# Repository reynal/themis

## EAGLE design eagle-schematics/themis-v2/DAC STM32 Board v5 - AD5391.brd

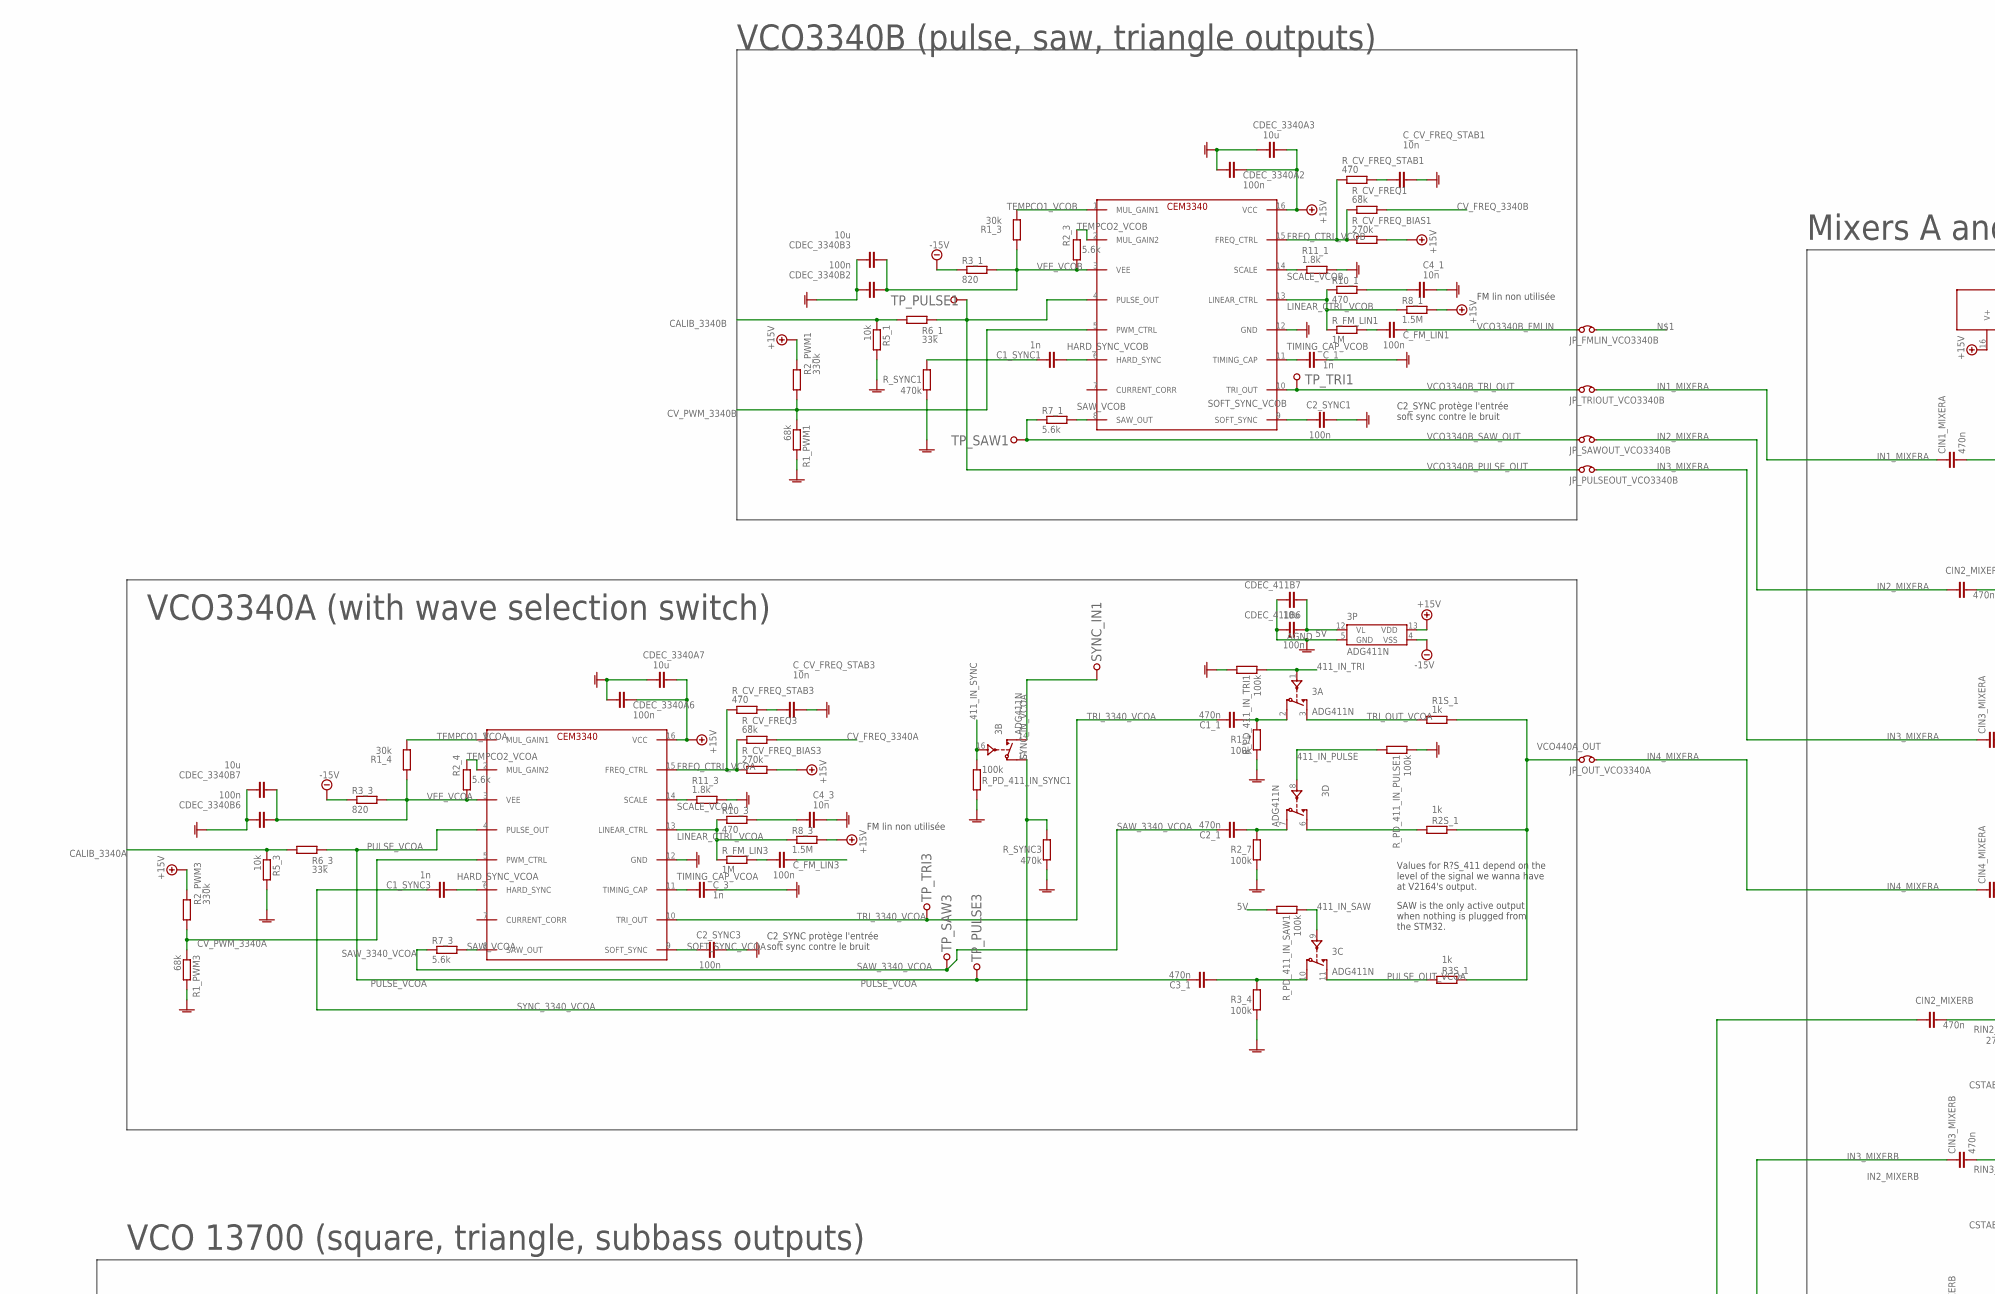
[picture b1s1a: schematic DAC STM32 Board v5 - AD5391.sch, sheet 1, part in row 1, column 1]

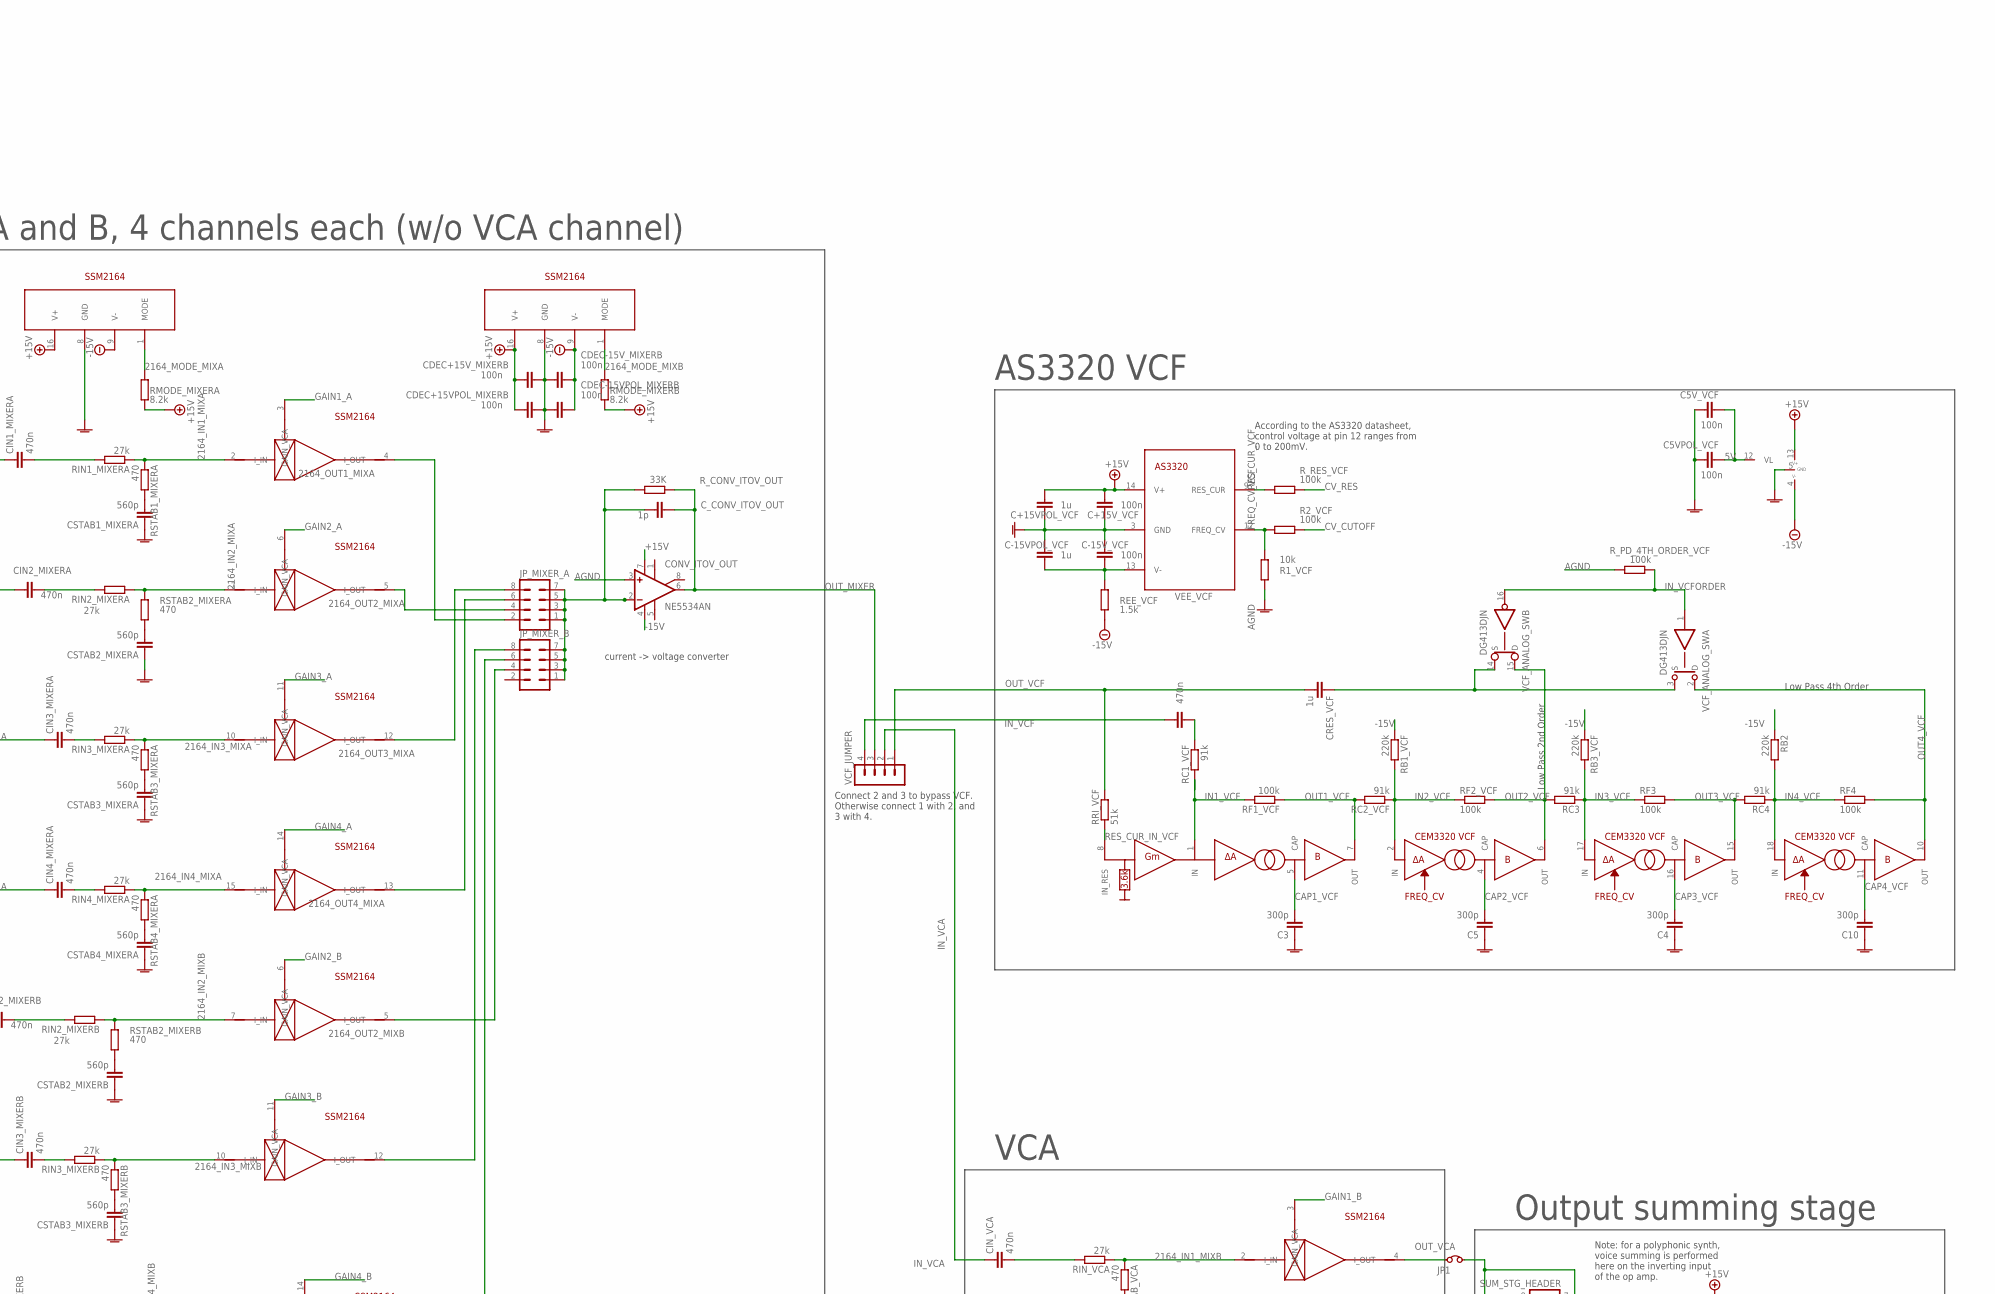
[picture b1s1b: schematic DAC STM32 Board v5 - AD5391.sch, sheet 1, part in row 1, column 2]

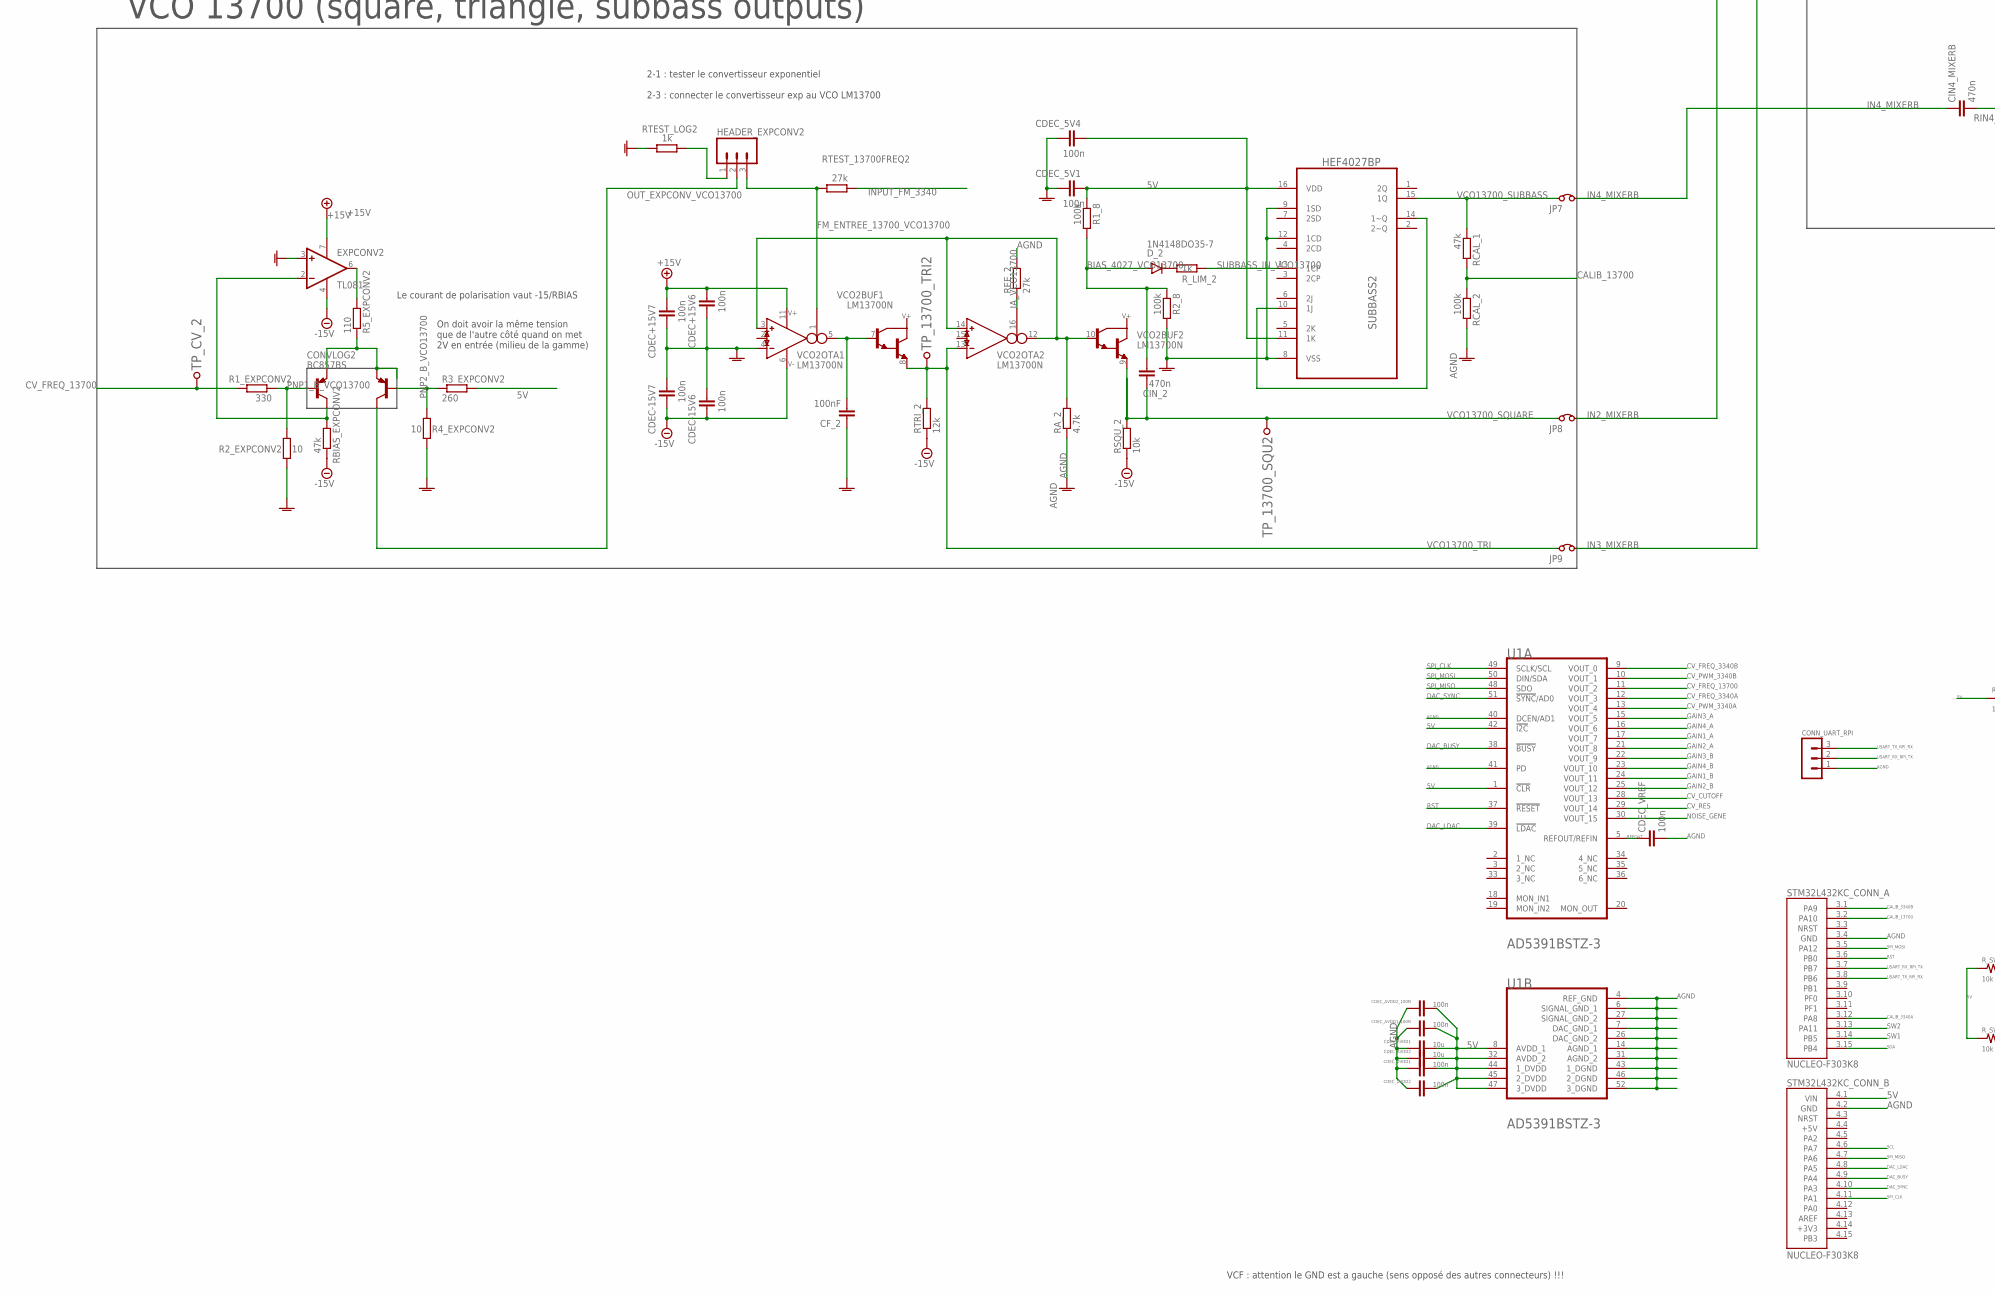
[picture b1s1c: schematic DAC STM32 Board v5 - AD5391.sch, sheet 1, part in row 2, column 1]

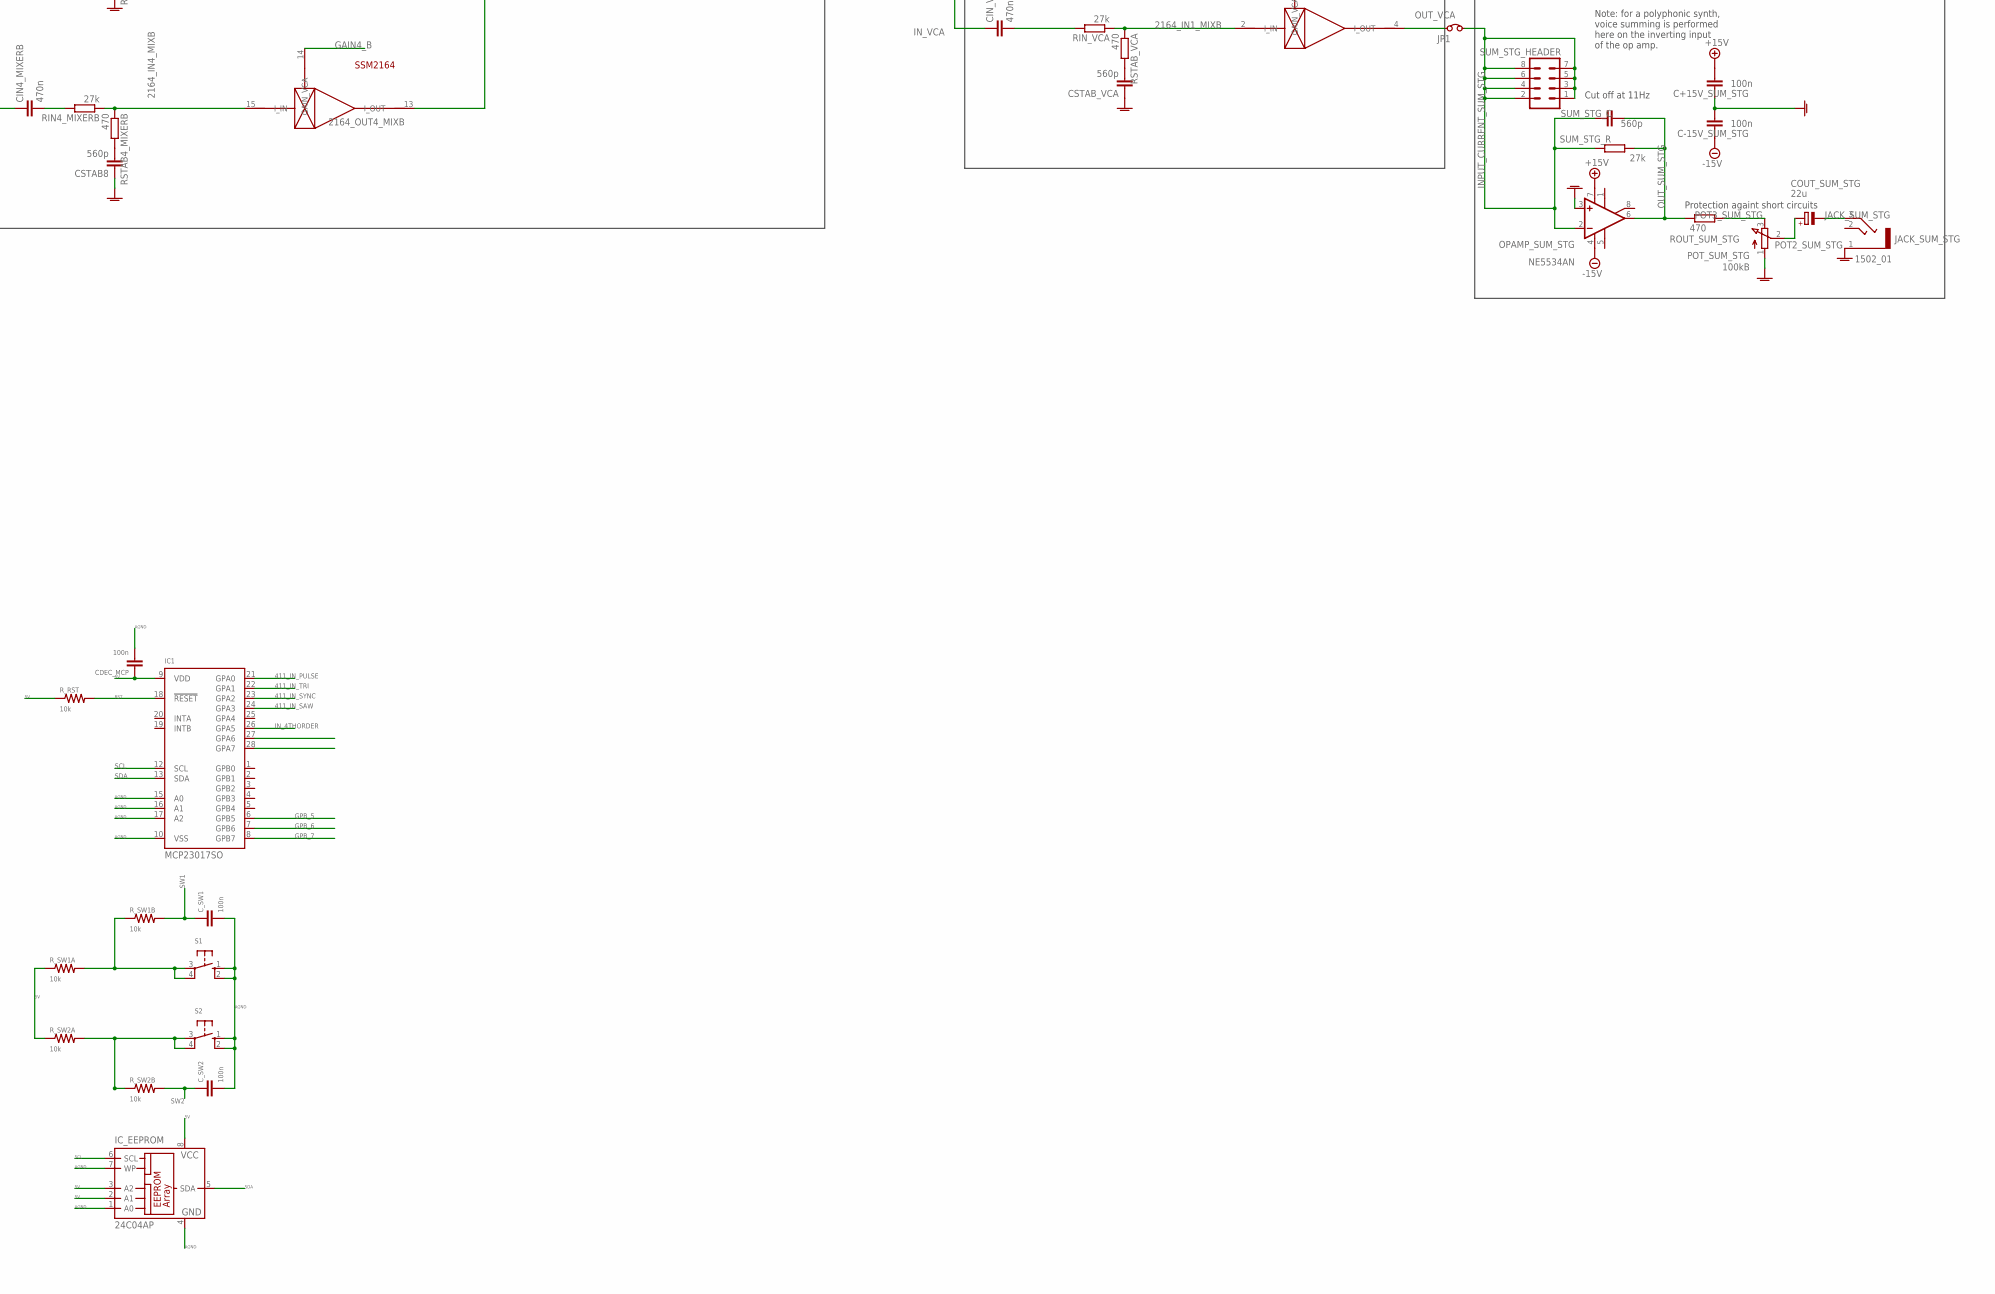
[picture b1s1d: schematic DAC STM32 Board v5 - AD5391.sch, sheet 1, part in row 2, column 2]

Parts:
3: ADG411N; DIL16
C1_1, C2_1: 470n; C075-032X103
C1_SYNC1, C1_SYNC3: 1n; C075-032X103
C2_SYNC1, C5VPOL_VCF, C5V_VCF: 100n; C075-032X103
C2_SYNC3: 100n; C050-025X075
C3, C4, C5, C10: 300p; C075-032X103
C3_1: 470n; C102-043X133
C4_1, C4_3: 10n; C050-025X075
C+15VPOL_VCF: 1u; C075-032X103
C+15V_SUM_STG, C+15V_VCF: 100n; C075-032X103
C-15VPOL_VCF: 1u; C075-032X103
C-15V_SUM_STG, C-15V_VCF: 100n; C075-032X103
CDEC+15V6, CDEC+15VPOL_MIXERB: 100n; C075-032X103
CDEC+15V7: 100n; C050-025X075
CDEC+15V_MIXERB: 100n; C050-030X075
CDEC-15V6: 100n; C050-025X075
CDEC-15V7: 100n; C075-032X103
CDEC-15VPOL_MIXERB, CDEC-15V_MIXERB: 100n; C050-030X075
CDEC_5V1, CDEC_5V4, CDEC_411B6, CDEC_3340A2, CDEC_3340A6, CDEC_3340B2, CDEC_3340B6: 100n; C050-025X075
CDEC_411B7, CDEC_3340A7, CDEC_3340B3, CDEC_3340B7: 10u; C050-025X075
CDEC_3340A3: 10u; C075-032X103
CDEC_AVDD1, CDEC_AVDD2: 10u; C050-030X075
CDEC_AVDD1_100N, CDEC_AVDD2_100N: 100n; C050-030X075
CDEC_DVDD1: 100n; C075-032X103
CDEC_DVDD2: 100n; C050-030X075
CDEC_MCP: 100n; C075-032X103
CDEC_VREF: 100n; C050-030X075
CEM1, CEM3: CEM3340; DIL16
CF_2: 100nF; C050-025X075
CIN1_MIXERA, CIN2_MIXERA, CIN2_MIXERB, CIN3_MIXERA, CIN3_MIXERB, CIN4_MIXERA, CIN4_MIXERB: 470n; C050-030X075
CIN_2: 470n; C050-025X075
CIN_VCA: 470n; C050-030X075
CONN_UART_RPI: MA03-1
CONVLOG2: BC857BS; DIL06
CONV_ITOV_OUT: NE5534AN; DIL08
COUT_SUM_STG: 22u; B45181A
CRES_VCF: 1u; C075-032X103
CSTAB1_MIXERA, CSTAB2_MIXERA, CSTAB2_MIXERB, CSTAB3_MIXERA, CSTAB3_MIXERB, CSTAB4_MIXERA, CSTAB8: 560p; C050-030X075
CSTAB_VCA: 560p; C050-030X075
C_1, C_3: 1n; C050-025X075
C_CONV_ITOV_OUT: 1p; C050-030X075
C_CV_FREQ_STAB1, C_CV_FREQ_STAB3: 10n; C075-032X103
C_FM_LIN1, C_FM_LIN3: 100n; C050-025X075
C_IN2: 470n; C050-025X075
C_SW1, C_SW2: 100n; C050-030X075
D_2: 1N4148DO35-7; DO35-7
EXPCONV2: TL081; DIL08
HEADER_EXPCONV2: M03; 03P
IC1: MCP23017SO; SO28W
IC_EEPROM: 24C04AP; DIL8
JACK_SUM_STG: 1502_01
JP1, JP7, JP8, JP9: JUMPER; HDR2X1
JP_FMLIN_VCO3340B: JUMPER; HDR2X1
JP_MIXER_A: MA04-2
JP_MIXER_B: MA04-2
JP_OUT_VCO3340A: JUMPER; HDR2X1
JP_PULSEOUT_VCO3340B: JUMPER; HDR2X1
JP_SAWOUT_VCO3340B: JUMPER; HDR2X1
JP_TRIOUT_VCO3340B: JUMPER; HDR2X1
MIXER_A: SSM2164_MULTI; DIL16
MIXER_B: SSM2164_MULTI; DIL16
OPAMP_SUM_STG: NE5534AN; DIL08
POT_SUM_STG: 100kB; 3RP/1610N
R1S_1, R2S_1: 1k; 0204/7
R1_3, R1_4: 30k; 0204/7
R1_7, R1_8, R2_8, R2_VCF: 100k; 0204/7
R1_EXPCONV2: 330; 0204/7
R1_PWM1: 68k; 0204/7
R1_PWM3: 68k; 0207/10
R1_VCF, R5_1, R5_3: 10k; 0204/7
R2_3, R2_4: 5.6k; 0204/7
R2_7, R3_4: 100k; 0207/10
R2_EXPCONV2, R4_EXPCONV2: 10; 0204/7
R2_PWM1, R2_PWM3: 330k; 0204/7
R3S_1: 1k; 0207/10
R3_1, R3_3: 820; 0204/7
R3_EXPCONV2: 260; 0204/7
R5_EXPCONV2: 110; 0204/7
R6_1, R6_3: 33k; 0204/7
R7_1, R7_3: 5.6k; 0207/10
R8_1, R8_3: 1.5M; 0204/7
R10_1, R10_3: 470; 0204/7
R11_1, R11_3: 1.8k; 0204/7
RA_2: 4.7k; 0204/7
RB1_VCF, RB2, RB3_VCF: 220k; 0204/7
RBIAS_EXPCONV2: 47k; 0204/7
RC1_VCF, RC2_VCF, RC3, RC4: 91k; 0204/7
RCAL_1: 47k; 0204/7
RCAL_2: 100k; 0204/7
REE_2: 27k; 0204/7
REE_VCF: 1.5k; 0207/10
RF1_VCF: 100k; 0207/10
RF2_VCF, RF3, RF4: 100k; 0204/7
RIN1_MIXERA, RIN2_MIXERB, RIN3_MIXERA, RIN3_MIXERB, RIN4_MIXERA, RIN4_MIXERB: 27k; 0204/7
RIN2_MIXERA: 27k; 0207/10
RIN_VCA: 27k; 0204/7
RMODE_MIXERA: 8.2k; 0204/7
RMODE_MIXERB: 8.2k; 0204/7
ROUT_SUM_STG: 470; 0207/12
RRI_VCF: 51k; 0207/10
RSQU_2: 10k; 0204/7
RSTAB1_MIXERA, RSTAB3_MIXERA, RSTAB3_MIXERB, RSTAB4_MIXERA, RSTAB4_MIXERB: 470; 0204/7
RSTAB2_MIXERA, RSTAB2_MIXERB: 470; 0207/10
RSTAB_VCA: 470; 0204/7
RTEST_13700FREQ2: 27k; 0204/7
RTEST_LOG2: 1k; 0204/7
RTRI_2: 12k; 0204/7
R_CONV_ITOV_OUT: 33K; 0204/7
R_CV_FREQ1, R_CV_FREQ3: 68k; 0204/7
R_CV_FREQ_BIAS1, R_CV_FREQ_BIAS3: 270k; 0204/7
R_CV_FREQ_STAB1, R_CV_FREQ_STAB3: 470; 0204/7
R_FM_LIN1, R_FM_LIN3: 1M; 0204/7
R_LIM_2: 1k; 0204/7
R_PD_4TH_ORDER_VCF, R_PD_411_IN_SAW1, R_PD_411_IN_SYNC1, R_PD_411_IN_TRI1: 100k; 0204/7
R_PD_411_IN_PULSE1: 100k; 0207/10
R_RES_VCF: 100k; 0204/7
R_RST: 10k; 0207/10
R_SW1A, R_SW1B, R_SW2A, R_SW2B: 10k; 0207/10
R_SYNC1, R_SYNC3: 470k; 0204/7
S1, S2: 10-XX; B3F-10XX
STM32L432KC_CONN_: NUCLEO-F303K8; MODULE_NUCLEO-F303K8
SUBBASS2: HEF4027BP; DIP254P762X420-16
SUM_STG_C: 560p; C075-032X103
SUM_STG_HEADER: MA04-2
SUM_STG_R: 27k; 0207/10
SYNC_IN1: TESTPOINT; TESTPOINT_63
TP_13700_SQU2, TP_13700_TRI2: TESTPOINT; TESTPOINT_63
TP_CV_2: TESTPOINT; TESTPOINT_63
TP_PULSE1, TP_PULSE3: TESTPOINT; TESTPOINT_63
TP_SAW1, TP_SAW3: TESTPOINT; TESTPOINT_63
TP_TRI1, TP_TRI3: TESTPOINT; TESTPOINT_63
U1: ANALOG_DEVICES_AD5391BSTZ-3ANALOG_DEVICES_AD5391B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; ANALOG_DEVICES_AD5391BSTZ-3_0
VCF: AS3320; DIL18
VCF_ANALOG_SW: DG413DJN; DIL16
VCF_JUMPER: MA04-1
VCO2: LM13700N; DIL16

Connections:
5V: 3.12 (VL), C5VPOL_VCF.1, C5V_VCF.1, CDEC_5V1.1, CDEC_5V4.1, CDEC_411B6.1, CDEC_411B7.1, CDEC_AVDD1.2, CDEC_AVDD1_100N.2, CDEC_AVDD2.2, CDEC_AVDD2_100N.2, CDEC_DVDD1.2, CDEC_DVDD2.2, CDEC_MCP.1, IC1.9 (VDD), IC_EEPROM.2 (A1), IC_EEPROM.3 (A2), IC_EEPROM.8 (VCC), R1_8.1, R3_EXPCONV2.2, R_PD_411_IN_SAW1.2, R_RST.1, R_SW1A.1, R_SW2A.1, STM32L432KC_CONN_.4.1 (VIN), SUBBASS2.11 (1K), SUBBASS2.16 (VDD), U1.1 (!CLR!), U1.8 (AVDD_1), U1.32 (AVDD_2), U1.42 (!I2C!), U1.44 (1_DVDD), U1.45 (2_DVDD), U1.47 (3_DVDD), VCF_ANALOG_SW.12 (VL)
411_IN_PULSE: 3.8 (IN), IC1.21 (GPA0), R_PD_411_IN_PULSE1.2
411_IN_SAW: 3.9 (IN), IC1.24 (GPA3), R_PD_411_IN_SAW1.1
411_IN_SYNC: 3.16 (IN), IC1.23 (GPA2), R_PD_411_IN_SYNC1.1
411_IN_TRI: 3.1 (IN), IC1.22 (GPA1), R_PD_411_IN_TRI1.1
2164_IN1_MIXA: MIXER_A.2 (I_IN), RIN1_MIXERA.1, RSTAB1_MIXERA.1
2164_IN1_MIXB: MIXER_B.2 (I_IN), RIN_VCA.1, RSTAB_VCA.1
2164_IN2_MIXA: MIXER_A.7 (I_IN), RIN2_MIXERA.1, RSTAB2_MIXERA.1
2164_IN2_MIXB: MIXER_B.7 (I_IN), RIN2_MIXERB.1, RSTAB2_MIXERB.1
2164_IN3_MIXA: MIXER_A.10 (I_IN), RIN3_MIXERA.1, RSTAB3_MIXERA.1
2164_IN3_MIXB: MIXER_B.10 (I_IN), RIN3_MIXERB.1, RSTAB3_MIXERB.1
2164_IN4_MIXA: MIXER_A.15 (I_IN), RIN4_MIXERA.1, RSTAB4_MIXERA.1
2164_IN4_MIXB: MIXER_B.15 (I_IN), RIN4_MIXERB.1, RSTAB4_MIXERB.1
2164_MODE_MIXA: MIXER_A.1 (MODE), RMODE_MIXERA.2
2164_MODE_MIXB: MIXER_B.1 (MODE), RMODE_MIXERB.2
2164_OUT1_MIXA: JP_MIXER_A.2, MIXER_A.4 (I_OUT)
2164_OUT2_MIXA: JP_MIXER_A.4, MIXER_A.5 (I_OUT)
2164_OUT2_MIXB: JP_MIXER_B.4, MIXER_B.5 (I_OUT)
2164_OUT3_MIXA: JP_MIXER_A.8, MIXER_A.12 (I_OUT)
2164_OUT3_MIXB: JP_MIXER_B.8, MIXER_B.12 (I_OUT)
2164_OUT4_MIXA: JP_MIXER_A.6, MIXER_A.13 (I_OUT)
2164_OUT4_MIXB: JP_MIXER_B.6, MIXER_B.13 (I_OUT)
+15V: 3.13 (VDD), C+15VPOL_VCF.2, C+15V_SUM_STG.2, C+15V_VCF.2, CDEC+15V6.1, CDEC+15V7.1, CDEC+15VPOL_MIXERB.2, CDEC+15V_MIXERB.2, CDEC_3340A2.2, CDEC_3340A3.2, CDEC_3340A6.2, CDEC_3340A7.2, CEM1.16 (VCC), CEM3.16 (VCC), CONV_ITOV_OUT.7 (V+), EXPCONV2.7 (V+), MIXER_A.16 (V+), MIXER_B.16 (V+), OPAMP_SUM_STG.7 (V+), R2_PWM1.2, R2_PWM3.2, R8_1.2, R8_3.2, RMODE_MIXERA.1, RMODE_MIXERB.1, R_CV_FREQ_BIAS1.2, R_CV_FREQ_BIAS3.2, VCF.14 (V+), VCF_ANALOG_SW.13 (V+), VCO2.11 (V+)
-15V: 3.4 (VSS), C-15V_SUM_STG.1, CDEC-15V6.2, CDEC-15V7.2, CDEC-15VPOL_MIXERB.1, CDEC-15V_MIXERB.1, CONV_ITOV_OUT.4 (V-), EXPCONV2.4 (V-), MIXER_A.9 (V-), MIXER_B.9 (V-), OPAMP_SUM_STG.4 (V-), R3_1.1, R3_3.1, RB1_VCF.1, RB2.1, RB3_VCF.1, RBIAS_EXPCONV2.1, REE_VCF.1, RSQU_2.1, RTRI_2.1, VCF_ANALOG_SW.4 (V-), VCO2.6 (V-)
AGND: 3.5 (GND), C2_SYNC1.1, C2_SYNC3.1, C3.1, C4.1, C4_1.2, C4_3.2, C5.1, C5VPOL_VCF.2, C5V_VCF.2, C10.1, C+15VPOL_VCF.1, C+15V_SUM_STG.1, C+15V_VCF.1, C-15VPOL_VCF.2, C-15V_SUM_STG.2, C-15V_VCF.2, CDEC+15V6.2, CDEC+15V7.2, CDEC+15VPOL_MIXERB.1, CDEC+15V_MIXERB.1, CDEC-15V6.1, CDEC-15V7.1, CDEC-15VPOL_MIXERB.2, CDEC-15V_MIXERB.2, CDEC_5V1.2, CDEC_5V4.2, CDEC_411B6.2, CDEC_411B7.2, CDEC_3340A2.1, CDEC_3340A3.1, CDEC_3340A6.1, CDEC_3340A7.1, CDEC_3340B2.1, CDEC_3340B3.1, CDEC_3340B6.1, CDEC_3340B7.1, CDEC_AVDD1.1, CDEC_AVDD1_100N.1, CDEC_AVDD2.1, CDEC_AVDD2_100N.1, CDEC_DVDD1.1, CDEC_DVDD2.1, CDEC_MCP.2, CDEC_VREF.2, CEM1.12 (GND), CEM3.12 (GND), CF_2.1, CONN_UART_RPI.1, CONV_ITOV_OUT.3 (+IN), CSTAB1_MIXERA.1, CSTAB2_MIXERA.1, CSTAB2_MIXERB.1, CSTAB3_MIXERA.1, CSTAB3_MIXERB.1, CSTAB4_MIXERA.1, CSTAB_VCA.1, C_1.1, C_3.1, C_CV_FREQ_STAB1.1, C_CV_FREQ_STAB3.1, C_SW1.2, C_SW2.2, EXPCONV2.3 (+IN), IC1.10 (VSS), IC1.15 (A0), IC1.16 (A1), IC1.17 (A2), IC_EEPROM.1 (A0), IC_EEPROM.4 (GND), IC_EEPROM.7 (WP), JACK_SUM_STG.1, MIXER_A.8 (GND), MIXER_B.8 (GND), OPAMP_SUM_STG.3 (+IN), POT_SUM_STG.1 (A), R1_7.1, R1_PWM1.2, R1_PWM3.2, R1_VCF.2, R2_7.1, R2_8.2, R2_EXPCONV2.2, R3_4.1, R4_EXPCONV2.2, R5_1.2, R5_3.2, R11_1.2, R11_3.2, RA_2.1, RCAL_2.2, REE_2.2, RTEST_LOG2.2, R_PD_4TH_ORDER_VCF.1, R_PD_411_IN_PULSE1.1, R_PD_411_IN_SYNC1.2, R_PD_411_IN_TRI1.2, R_SYNC1.1, R_SYNC3.1, S1.1 (S), S1.2 (S1), S2.1 (S), S2.2 (S1), STM32L432KC_CONN_.3.4 (GND), STM32L432KC_CONN_.4.2 (GND), SUBBASS2.8 (VSS), SUBBASS2.9 (1SD), SUBBASS2.12 (1CD), U1.4 (REF_GND), U1.6 (SIGNAL_GND_1), U1.7 (DAC_GND_1), U1.14 (AGND_1), U1.26 (DAC_GND_2), U1.27 (SIGNAL_GND_2), U1.31 (AGND_2), U1.40 (DCEN/AD1), U1.41 (PD), U1.43 (1_DGND), U1.46 (2_DGND), U1.52 (3_DGND), VCF.3 (GND), VCF_ANALOG_SW.5 (GND), VCO2.4 (IN_N)
BIAS_4027_VCO13700: CIN_2.1, D_2.A, R1_8.2, R2_8.1
CALIB_3340A: R5_3.1, R6_3.1, STM32L432KC_CONN_.3.12 (PA8)
CALIB_3340B: R5_1.1, R6_1.1, STM32L432KC_CONN_.3.1 (PA9)
CALIB_13700: RCAL_1.2, RCAL_2.1, STM32L432KC_CONN_.3.2 (PA10)
CAP1_VCF: C3.2, VCF.5 (CAP)
CAP2_VCF: C5.2, VCF.4 (CAP)
CAP3_VCF: C4.2, VCF.16 (CAP)
CAP4_VCF: C10.2, VCF.11 (CAP)
CSTAB3_MIXERB: CSTAB8.1
CV_CUTOFF: R2_VCF.2, U1.28 (VOUT_13)
CV_FREQ_3340A: R_CV_FREQ3.2, U1.12 (VOUT_3)
CV_FREQ_3340B: R_CV_FREQ1.2, U1.9 (VOUT_0)
CV_FREQ_13700: R1_EXPCONV2.2, TP_CV_2.P$1, U1.11 (VOUT_2)
CV_PWM_3340A: CEM3.5 (PWM_CTRL), R1_PWM3.1, R2_PWM3.1, U1.13 (VOUT_4)
CV_PWM_3340B: CEM1.5 (PWM_CTRL), R1_PWM1.1, R2_PWM1.1, U1.10 (VOUT_1)
CV_RES: R_RES_VCF.2, U1.29 (VOUT_14)
DAC_BUSY: STM32L432KC_CONN_.4.9 (PA4), U1.38 (!BUSY!)
DAC_LDAC: STM32L432KC_CONN_.4.8 (PA5), U1.39 (!LDAC!)
DAC_SYNC: STM32L432KC_CONN_.4.10 (PA3), U1.51 (!SYNC!/AD0)
FM_ENTREE_13700_VCO13700: HEADER_EXPCONV2.3, RTEST_13700FREQ2.2, VCO2.1 (I_BIAS)
FREQ_CTRL_VCOA: CEM3.15 (FREQ_CTRL), R_CV_FREQ3.1, R_CV_FREQ_BIAS3.1, R_CV_FREQ_STAB3.1
FREQ_CTRL_VCOB: CEM1.15 (FREQ_CTRL), R_CV_FREQ1.1, R_CV_FREQ_BIAS1.1, R_CV_FREQ_STAB1.1
FREQ_CV_VCF: R1_VCF.1, R2_VCF.1, VCF.12 (FREQ_CV)
GAIN1_A: MIXER_A.3 (GAIN_VCA), U1.17 (VOUT_7)
GAIN1_B: MIXER_B.3 (GAIN_VCA), U1.24 (VOUT_11)
GAIN2_A: MIXER_A.6 (GAIN_VCA), U1.21 (VOUT_8)
GAIN2_B: MIXER_B.6 (GAIN_VCA), U1.25 (VOUT_12)
GAIN3_A: MIXER_A.11 (GAIN_VCA), U1.15 (VOUT_5)
GAIN3_B: MIXER_B.11 (GAIN_VCA), U1.22 (VOUT_9)
GAIN4_A: MIXER_A.14 (GAIN_VCA), U1.16 (VOUT_6)
GAIN4_B: MIXER_B.14 (GAIN_VCA), U1.23 (VOUT_10)
GPB_5: IC1.6 (GPB5)
GPB_6: IC1.7 (GPB6)
GPB_7: IC1.8 (GPB7)
HARD_SYNC_VCOA: C1_SYNC3.2, CEM3.6 (HARD_SYNC)
HARD_SYNC_VCOB: C1_SYNC1.2, CEM1.6 (HARD_SYNC)
IA_VCO13700: REE_2.1, VCO2.16 (I_BIAS)
IN1_MIXERA: CIN1_MIXERA.1, JP_TRIOUT_VCO3340B.2
IN1_VCF: RC1_VCF.2, RF1_VCF.2, VCF.1 (IN)
IN2_MIXERA: CIN2_MIXERA.1, JP_SAWOUT_VCO3340B.2
IN2_MIXERB: CIN2_MIXERB.1, JP8.2
IN2_VCF: RB1_VCF.2, RC2_VCF.1, RF2_VCF.1, VCF.2 (IN)
IN3_MIXERA: CIN3_MIXERA.1, JP_PULSEOUT_VCO3340B.2
IN3_MIXERB: CIN3_MIXERB.1, JP9.2
IN3_VCF: RB3_VCF.2, RC3.1, RF3.1, VCF.17 (IN)
IN4_MIXERA: CIN4_MIXERA.1, JP_OUT_VCO3340A.2
IN4_MIXERB: CIN4_MIXERB.1, JP7.2
IN4_VCF: RB2.2, RC4.1, RF4.1, VCF.18 (IN)
INPUT_CURRENT_SUM_STG: JP1.2, OPAMP_SUM_STG.2 (-IN), SUM_STG_C.2, SUM_STG_HEADER.1, SUM_STG_HEADER.2, SUM_STG_HEADER.3, SUM_STG_HEADER.4, SUM_STG_HEADER.5, SUM_STG_HEADER.6, SUM_STG_HEADER.7, SUM_STG_HEADER.8, SUM_STG_R.2
INPUT_FM_3340: RTEST_13700FREQ2.1
IN_4THORDER: IC1.26 (GPA5)
IN_VCA: CIN_VCA.1, VCF_JUMPER.2
IN_VCF: C_IN2.2, VCF_JUMPER.4
IN_VCFORDER: R_PD_4TH_ORDER_VCF.2, VCF_ANALOG_SW.1 (IN), VCF_ANALOG_SW.16 (IN)
JACK_SUM_STG: COUT_SUM_STG.-, JACK_SUM_STG.3 (2)
LINEAR_CTRL_VCOA: CEM3.13 (LINEAR_CTRL), R8_3.1, R10_3.1, R_FM_LIN3.1
LINEAR_CTRL_VCOB: CEM1.13 (LINEAR_CTRL), R8_1.1, R10_1.1, R_FM_LIN1.1
MIXER_OUT1: CONV_ITOV_OUT.2 (-IN), C_CONV_ITOV_OUT.1, JP_MIXER_A.1, JP_MIXER_A.3, JP_MIXER_A.5, JP_MIXER_A.7, JP_MIXER_B.1, JP_MIXER_B.3, JP_MIXER_B.5, JP_MIXER_B.7, R_CONV_ITOV_OUT.1
unnamed: R_SW1A.2, R_SW1B.1, S1.3, S1.4 (P1)
unnamed: R_SW2A.2, R_SW2B.1, S2.3, S2.4 (P1)
unnamed: CSTAB2_MIXERB.2, RSTAB2_MIXERB.2
unnamed: CSTAB_VCA.2, RSTAB_VCA.2
unnamed: CSTAB3_MIXERB.2, RSTAB3_MIXERB.2
unnamed: CSTAB8.2, RSTAB4_MIXERB.2
unnamed: CIN_VCA.2, RIN_VCA.2
unnamed: CIN3_MIXERB.2, RIN3_MIXERB.2
unnamed: CIN2_MIXERB.2, RIN2_MIXERB.2
unnamed: CIN4_MIXERB.2, RIN4_MIXERB.2
unnamed: CSTAB2_MIXERA.2, RSTAB2_MIXERA.2
unnamed: CSTAB1_MIXERA.2, RSTAB1_MIXERA.2
unnamed: CSTAB3_MIXERA.2, RSTAB3_MIXERA.2
unnamed: CSTAB4_MIXERA.2, RSTAB4_MIXERA.2
unnamed: CIN1_MIXERA.2, RIN1_MIXERA.2
unnamed: CIN3_MIXERA.2, RIN3_MIXERA.2
unnamed: CIN2_MIXERA.2, RIN2_MIXERA.2
unnamed: CIN4_MIXERA.2, RIN4_MIXERA.2
unnamed: C_CV_FREQ_STAB1.2, R_CV_FREQ_STAB1.2
unnamed: C4_1.1, R10_1.2
unnamed: C_FM_LIN1.1, R_FM_LIN1.2
unnamed: C_CV_FREQ_STAB3.2, R_CV_FREQ_STAB3.2
unnamed: C4_3.1, R10_3.2
unnamed: 3.2 (D), C1_1.2, R1_7.2
unnamed: 3.7 (D), C2_1.2, R2_7.2
unnamed: 3.10 (D), C3_1.2, R3_4.2
unnamed: 3.6 (S), R2S_1.2
unnamed: C_FM_LIN3.1, R_FM_LIN3.2
unnamed: EXPCONV2.6 (OUT), R5_EXPCONV2.2
unnamed: RA_2.2, VCO2.3 (IN_P), VCO2.10 (B), VCO2.12 (OUT), VCO2.14 (IN_P)
unnamed: CF_2.2, VCO2.5 (OUT), VCO2.7 (B)
unnamed: SUBBASS2.10 (1J), SUBBASS2.14 (1~Q)
unnamed: D_2.C, R_LIM_2.2
unnamed: HEADER_EXPCONV2.1, RTEST_LOG2.1
unnamed: CRES_VCF.1, VCF_ANALOG_SW.3 (S), VCF_ANALOG_SW.14 (S)
unnamed: C_IN2.1, RC1_VCF.1
NOISE_GENE: U1.30 (VOUT_15)
OUT1_VCF: RC2_VCF.2, RF1_VCF.1, VCF.7 (OUT)
OUT2_VCF: RC3.2, RF2_VCF.2, VCF.6 (OUT), VCF_ANALOG_SW.15 (D)
OUT3_VCF: RC4.2, RF3.2, VCF.15 (OUT)
OUT4_VCF: RF4.2, VCF.10 (OUT), VCF_ANALOG_SW.2 (D)
OUT_EXPCONV_VCO13700: CONVLOG2.3 (C2), HEADER_EXPCONV2.2
OUT_MIXER: CONV_ITOV_OUT.6 (OUT), C_CONV_ITOV_OUT.2, R_CONV_ITOV_OUT.2, VCF_JUMPER.3
OUT_SUM_STG: OPAMP_SUM_STG.6 (OUT), ROUT_SUM_STG.2, SUM_STG_C.1, SUM_STG_R.1
OUT_VCA: JP1.1, MIXER_B.4 (I_OUT)
OUT_VCF: CRES_VCF.2, RRI_VCF.2, VCF_JUMPER.1
PNP1_B_VCO13700: CONVLOG2.2 (B1), R1_EXPCONV2.1, R2_EXPCONV2.1
PNP1_C1_VCO1: CONVLOG2.6 (C1), EXPCONV2.2 (-IN), RBIAS_EXPCONV2.2
PNP2_B_VCO13700: CONVLOG2.5 (B2), R3_EXPCONV2.1, R4_EXPCONV2.1
PNP_E1-VCO1_MIXB: CONVLOG2.1 (E1), CONVLOG2.4 (E2), R5_EXPCONV2.1
POT2_SUM_STG: COUT_SUM_STG.+, POT_SUM_STG.2 (S)
POT3_SUM_STG: POT_SUM_STG.3 (E), ROUT_SUM_STG.1
PULSE_OUT_VCOA: 3.11 (S), R3S_1.2
PULSE_VCOA: C3_1.1, CEM3.4 (PULSE_OUT), R6_3.2, TP_PULSE3.P$1
REFOUT: CDEC_VREF.1, U1.5 (REFOUT/REFIN)
RES_CUR_IN_VCF: RRI_VCF.1, VCF.8 (IN_RES)
RES_CUR_VCF: R_RES_VCF.1, VCF.9 (RES_CUR)
RST: IC1.18 (!RESET), R_RST.2, STM32L432KC_CONN_.3.6 (PB0), U1.37 (!RESET!)
SAW_3340_VCOA: C2_1.1, R7_3.1, TP_SAW3.P$1
SAW_VCOA: CEM3.8 (SAW_OUT), R7_3.2
SAW_VCOB: CEM1.8 (SAW_OUT), R7_1.2
SCALE_VCOA: CEM3.14 (SCALE), R11_3.1
SCALE_VCOB: CEM1.14 (SCALE), R11_1.1
SCL: IC1.12 (SCL), IC_EEPROM.6 (SCL), STM32L432KC_CONN_.4.6 (PA7)
SDA: IC1.13 (SDA), IC_EEPROM.5 (SDA), STM32L432KC_CONN_.3.15 (PB4)
SOFT_SYNC_VCOA: C2_SYNC3.2, CEM3.9 (SOFT_SYNC)
SOFT_SYNC_VCOB: C2_SYNC1.2, CEM1.9 (SOFT_SYNC)
SPI_CLK: STM32L432KC_CONN_.4.11 (PA1), U1.49 (SCLK/SCL)
SPI_MISO: STM32L432KC_CONN_.4.7 (PA6), U1.48 (SDO)
SPI_MOSI: STM32L432KC_CONN_.3.5 (PA12), U1.50 (DIN/SDA)
SUBBASS_IN_VCO13700: R_LIM_2.1, SUBBASS2.13 (1CP)
SW1: C_SW1.1, R_SW1B.2, STM32L432KC_CONN_.3.14 (PB5)
SW2: C_SW2.1, R_SW2B.2, STM32L432KC_CONN_.3.13 (PA11)
SYNC_3340_VCOA: 3.15 (D), C1_SYNC3.1, R_SYNC3.2
SYNC_3340_VCOB: C1_SYNC1.1, R_SYNC1.2
SYNC_IN_VCOA: 3.14 (S), SYNC_IN1.P$1
TEMPCO1_VCOA: CEM3.1 (MUL_GAIN1), R1_4.1
TEMPCO1_VCOB: CEM1.1 (MUL_GAIN1), R1_3.1
TEMPCO2_VCOA: CEM3.2 (MUL_GAIN2), R2_4.1
TEMPCO2_VCOB: CEM1.2 (MUL_GAIN2), R2_3.1
TIMING_CAP_VCOA: CEM3.11 (TIMING_CAP), C_3.2
TIMING_CAP_VCOB: CEM1.11 (TIMING_CAP), C_1.2
TRI_3340_VCOA: C1_1.1, CEM3.10 (TRI_OUT), TP_TRI3.P$1
TRI_OUT_VCOA: 3.3 (S), R1S_1.1
USART_RX_RPI_TX: CONN_UART_RPI.2, STM32L432KC_CONN_.3.7 (PB7)
USART_TX_RPI_RX: CONN_UART_RPI.3, STM32L432KC_CONN_.3.8 (PB6)
VCO440A_OUT: JP_OUT_VCO3340A.1, R1S_1.2, R2S_1.1, R3S_1.1
VCO3340B_FMLIN: C_FM_LIN1.2, JP_FMLIN_VCO3340B.1
VCO3340B_PULSE_OUT: CEM1.4 (PULSE_OUT), JP_PULSEOUT_VCO3340B.1, R6_1.2, TP_PULSE1.P$1
VCO3340B_SAW_OUT: JP_SAWOUT_VCO3340B.1, R7_1.1, TP_SAW1.P$1
VCO3340B_TRI_OUT: CEM1.10 (TRI_OUT), JP_TRIOUT_VCO3340B.1, TP_TRI1.P$1
VCO13700_SQUARE: CIN_2.2, JP8.1, RSQU_2.2, TP_13700_SQU2.P$1, VCO2.9 (E)
VCO13700_SUBBASS: JP7.1, RCAL_1.1, SUBBASS2.15 (1Q)
VCO13700_TRI: JP9.1, RTRI_2.2, TP_13700_TRI2.P$1, VCO2.8 (E), VCO2.13 (IN_N)
VEE_VCF: C-15VPOL_VCF.1, C-15V_VCF.1, REE_VCF.2, VCF.13 (V-)
VEE_VCOA: CDEC_3340B6.2, CDEC_3340B7.2, CEM3.3 (VEE), R1_4.2, R2_4.2, R3_3.2
VEE_VCOB: CDEC_3340B2.2, CDEC_3340B3.2, CEM1.3 (VEE), R1_3.2, R2_3.2, R3_1.2

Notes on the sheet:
VCF : attention le GND est a gauche (sens opposé des autres connecteurs) !!!
Note: for a polyphonic synth, voice summing is performed here on the inverting input of the op amp.
Output summing stage
Cut off at 11Hz
Protection againt short circuits
Mixers A and B, 4 channels each (w/o VCA channel)
current -> voltage converter
VCO3340B (pulse, saw, triangle outputs)
C2_SYNC protège l'entrée soft sync contre le bruit
FM lin non utilisée
VCO3340A (with wave selection switch)
Values for R?S_411 depend on the level of the signal we wanna have at V2164's output.
SAW is the only active output when nothing is plugged from the STM32.
On doit avoir la même tension que de l'autre côté quand on met 2V en entrée (milieu de la gamme)
Le courant de polarisation vaut -15/RBIAS
2-1 : tester le convertisseur exponentiel 2-3 : connecter le convertisseur exp au VCO LM13700
According to the AS3320 datasheet, control voltage at pin 12 ranges from 0 to 200mV.
AS3320 VCF
Low Pass 2nd Order
Low Pass 4th Order
VCA
VCO 13700 (square, triangle, subbass outputs)
Connect 2 and 3 to bypass VCF. Otherwise connect 1 with 2, and 3 with 4.

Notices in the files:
parts and their libraries:
microbuilder: This work is placed in the public domain, and may be freely used for commercial and non-commercial work with the following conditions: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
